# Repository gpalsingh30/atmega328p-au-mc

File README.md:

# atmega328p-au-mc
A condensed microcontroller based on the ATMEGA328P-AU designed to work in sub-zero temperatures. Primary applications include areas where other microcontrollers could not function due to low temperatures or near-space ballooning.

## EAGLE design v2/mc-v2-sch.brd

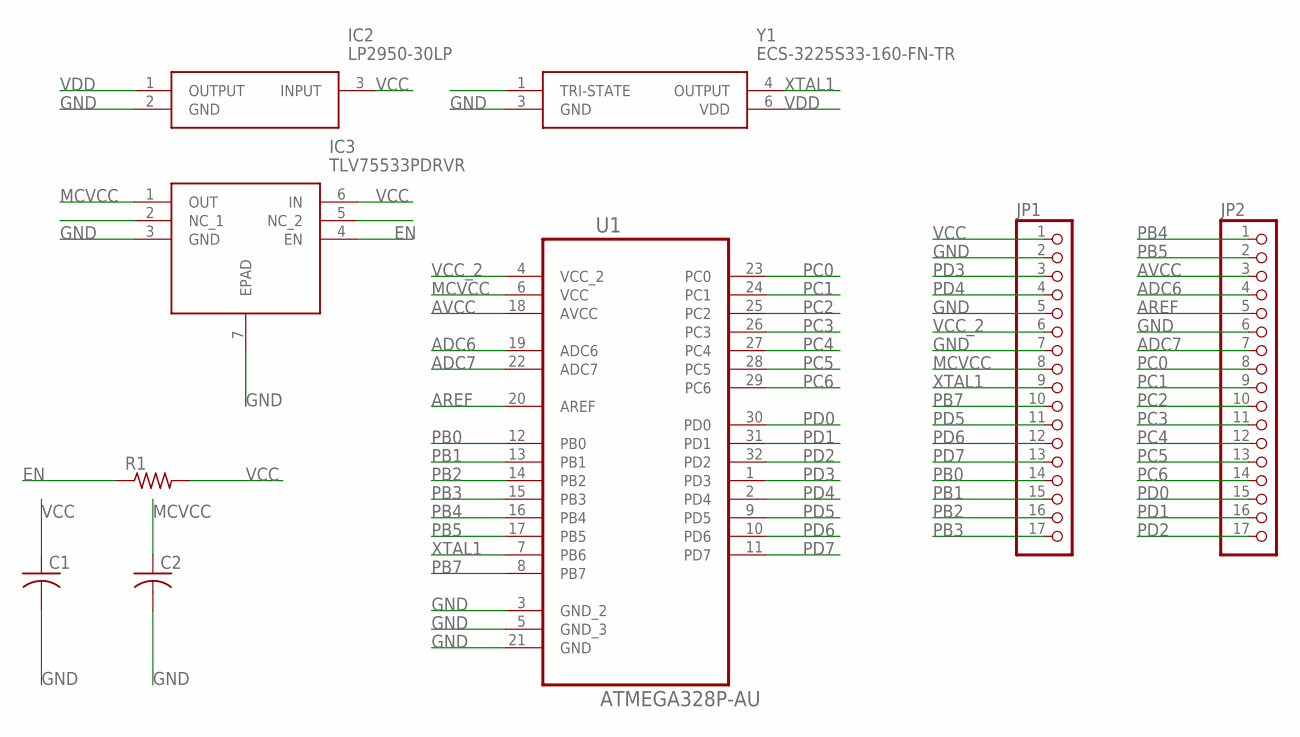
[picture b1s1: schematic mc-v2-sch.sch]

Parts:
C1, C2: C-USC1206; C1206
IC2: LP2950-30LP; LP0003A
IC3: TLV75533PDRVR; SON65P200X200X80-7N
JP1, JP2: PINHD-1X17; 1X17
R1: R-US_R0603; R0603
U1: ATMEGA328P-AU; QFP80P900X900X120-32N
Y1: ECS-3225S33-160-FN-TR; ECS3225S33200FNTR

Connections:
ADC6: JP2.4, U1.19 (ADC6)
ADC7: JP2.7, U1.22 (ADC7)
AREF: JP2.5, U1.20 (AREF)
AVCC: JP2.3, U1.18 (AVCC)
EN: IC3.4 (EN), R1.1
GND: C1.2, C2.2, IC2.2 (GND), IC3.3 (GND), IC3.7 (EPAD), JP1.2, JP1.5, JP1.7, JP2.6, U1.3 (GND_2), U1.5 (GND_3), U1.21 (GND), Y1.3 (GND)
MCVCC: C2.1, IC3.1 (OUT), JP1.8, U1.6 (VCC)
PB0: JP1.14, U1.12 (PB0)
PB1: JP1.15, U1.13 (PB1)
PB2: JP1.16, U1.14 (PB2)
PB3: JP1.17, U1.15 (PB3)
PB4: JP2.1, U1.16 (PB4)
PB5: JP2.2, U1.17 (PB5)
PB7: JP1.10, U1.8 (PB7)
PC0: JP2.8, U1.23 (PC0)
PC1: JP2.9, U1.24 (PC1)
PC2: JP2.10, U1.25 (PC2)
PC3: JP2.11, U1.26 (PC3)
PC4: JP2.12, U1.27 (PC4)
PC5: JP2.13, U1.28 (PC5)
PC6: JP2.14, U1.29 (PC6)
PD0: JP2.15, U1.30 (PD0)
PD1: JP2.16, U1.31 (PD1)
PD2: JP2.17, U1.32 (PD2)
PD3: JP1.3, U1.1 (PD3)
PD4: JP1.4, U1.2 (PD4)
PD5: JP1.11, U1.9 (PD5)
PD6: JP1.12, U1.10 (PD6)
PD7: JP1.13, U1.11 (PD7)
VCC: C1.1, IC2.3 (INPUT), IC3.6 (IN), JP1.1, R1.2
VCC_2: JP1.6, U1.4 (VCC_2)
VDD: IC2.1 (OUTPUT), Y1.6 (VDD)
XTAL1: JP1.9, U1.7 (PB6), Y1.4 (OUTPUT)

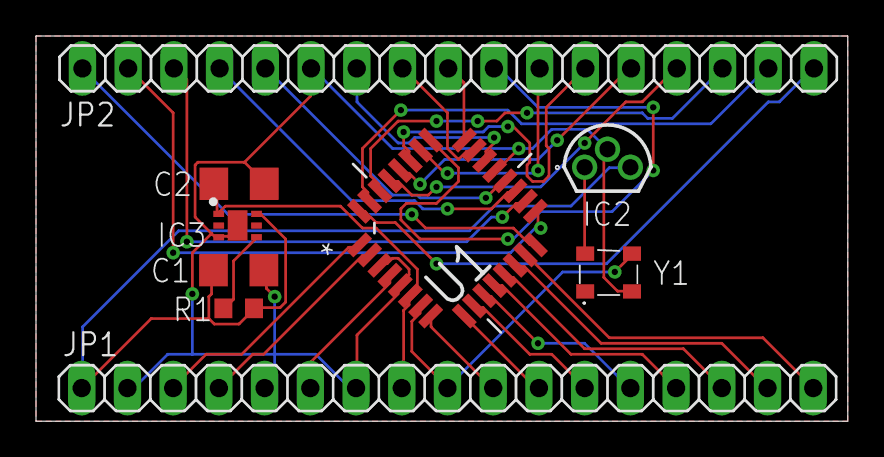
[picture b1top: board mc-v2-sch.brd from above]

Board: 2 copper layers, 45.1 x 21.4 mm, 9 parts (0 on the bottom side), 33 nets.

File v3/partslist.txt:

ATMEGA-MC V3 Parts List:
	-QTY-PART
	-1-LP2980AIM5-3.3/NOPB
	-1-TLV75533PDRVR
	-2-AC0603FR-104K75L
	-2-C1206X105K3RAC3316
	-1-ATMEGA328P-AU
	-1-ECS-3225S33-160-FN-TR

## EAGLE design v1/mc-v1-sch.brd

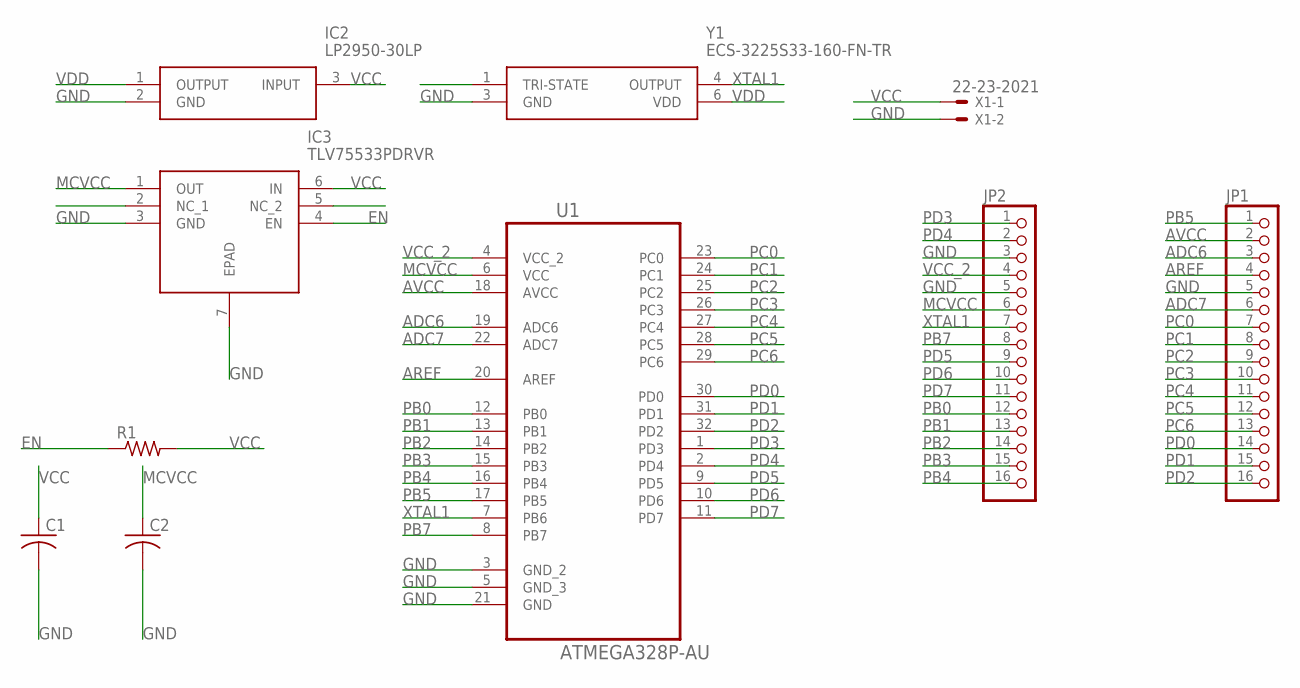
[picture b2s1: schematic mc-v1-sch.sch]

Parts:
C1, C2: C-USC1206; C1206
IC2: LP2950-30LP; LP0003A
IC3: TLV75533PDRVR; SON65P200X200X80-7N
JP1, JP2: PINHD-1X16; 1X16
R1: R-US_R0603; R0603
U1: ATMEGA328P-AU; QFP80P900X900X120-32N
X1: 22-23-2021
Y1: ECS-3225S33-160-FN-TR; ECS3225S33200FNTR

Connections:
ADC6: JP1.3, U1.19 (ADC6)
ADC7: JP1.6, U1.22 (ADC7)
AREF: JP1.4, U1.20 (AREF)
AVCC: JP1.2, U1.18 (AVCC)
EN: IC3.4 (EN), R1.1
GND: C1.2, C2.2, IC2.2 (GND), IC3.3 (GND), IC3.7 (EPAD), JP1.5, JP2.3, JP2.5, U1.3 (GND_2), U1.5 (GND_3), U1.21 (GND), X1.2, Y1.3 (GND)
MCVCC: C2.1, IC3.1 (OUT), JP2.6, U1.6 (VCC)
PB0: JP2.12, U1.12 (PB0)
PB1: JP2.13, U1.13 (PB1)
PB2: JP2.14, U1.14 (PB2)
PB3: JP2.15, U1.15 (PB3)
PB4: JP2.16, U1.16 (PB4)
PB5: JP1.1, U1.17 (PB5)
PB7: JP2.8, U1.8 (PB7)
PC0: JP1.7, U1.23 (PC0)
PC1: JP1.8, U1.24 (PC1)
PC2: JP1.9, U1.25 (PC2)
PC3: JP1.10, U1.26 (PC3)
PC4: JP1.11, U1.27 (PC4)
PC5: JP1.12, U1.28 (PC5)
PC6: JP1.13, U1.29 (PC6)
PD0: JP1.14, U1.30 (PD0)
PD1: JP1.15, U1.31 (PD1)
PD2: JP1.16, U1.32 (PD2)
PD3: JP2.1, U1.1 (PD3)
PD4: JP2.2, U1.2 (PD4)
PD5: JP2.9, U1.9 (PD5)
PD6: JP2.10, U1.10 (PD6)
PD7: JP2.11, U1.11 (PD7)
VCC: C1.1, IC2.3 (INPUT), IC3.6 (IN), R1.2, X1.1
VCC_2: JP2.4, U1.4 (VCC_2)
VDD: IC2.1 (OUTPUT), Y1.6 (VDD)
XTAL1: JP2.7, U1.7 (PB6), Y1.4 (OUTPUT)

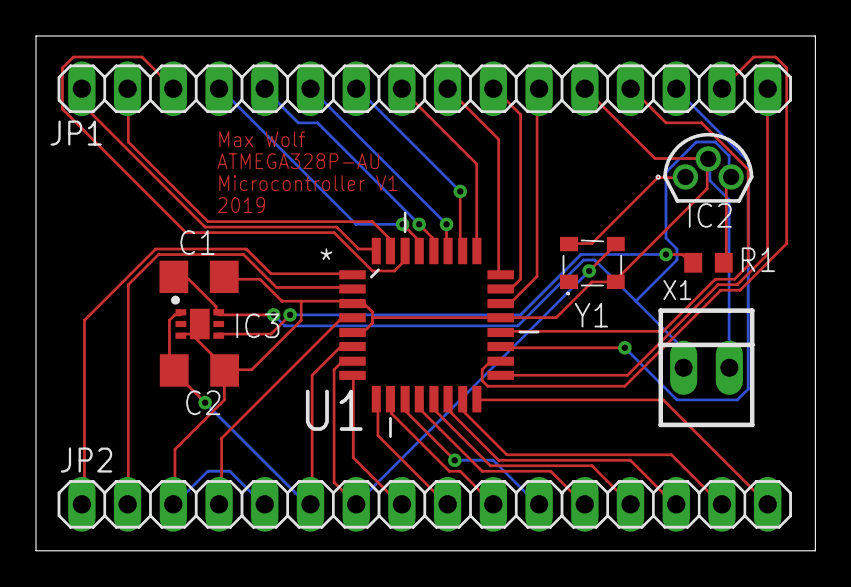
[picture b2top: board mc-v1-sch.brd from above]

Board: 2 copper layers, 43.3 x 28.6 mm, 10 parts (0 on the bottom side), 33 nets.

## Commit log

2019-07-21 Initial commit
    .brd and .sch files only.
2019-07-21 Create v1
2019-07-21 Rename mc-v1-sch.brd to v1/mc-v1-sch.brd
2019-07-21 Rename mc-v1-sch.sch to v1/mc-v1-sch.sch
2019-07-21 Create v2
